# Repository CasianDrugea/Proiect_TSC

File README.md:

# Documentație Tehnică - InkTime Smartwatch
## Student: Drugea Casian 332CA

## 1. Descrierea Generală a Sistemului
Proiectul **InkTime** este un dispozitiv purtabil bazat pe microcontrolerul **nRF52840**, proiectat pentru a oferi o autonomie ridicată prin utilizarea unui ecran de tip E-Paper. Sistemul integrează funcționalități de monitorizare a mișcării, interfață haptică și un management avansat al energiei, fiind optimizat pentru dimensiuni reduse și eficiență.

## 2. Diagrama Bloc
Arhitectura hardware este structurată în jurul nucleului ARM Cortex-M4F, interconectat cu următoarele module:

* **Sistem de Procesare:** nRF52840 (Bluetooth 5.0, GPIO, SPI, I2C).
* **Afișaj:** E-Paper Display (EPD) cu circuit de drive integrat.
* **Senzori & Haptics:** Accelerometru BMA423 și Driver Haptic DRV2605.
* **Management Energie:** Încărcător LiPo BQ25180, Fuel Gauge MAX17048 și convertor DC/DC RT610A.
* **Interfață Utilizator:** Trei butoane de control (Up, Enter, Down).

## 3. Funcționalitate Hardware și Interfețe
Dispozitivul utilizează următoarele soluții tehnice pentru realizarea funcțiilor sale:

* **Microcontroler (nRF52840):** Gestionează stiva de comunicație Bluetooth și coordonează toți perifericii. S-a optat pentru acest model datorită consumului redus în modurile de repaus și a unității de calcul în virgulă mobila (FPU).
* **Afișaj E-Paper:** Este controlat prin interfața **SPI**. Circuitul de drive (bazat pe inductorul L5 și diodele MBR0530) asigură tensiunile necesare pentru actualizarea pixelilor.
* **Managementul Bateriei:**
    * **BQ25180:** Gestionează încărcarea prin USB-C și monitorizează curentul de intrare.
    * **MAX17048:** Monitorizează tensiunea celulei LiPo și oferă un algoritm de calcul al stării de încărcare (SoC) prin I2C.
    * **RT610A:** Un convertor Buck-Boost care stabilizează tensiunea la 3.3V, indiferent de nivelul de descărcare al bateriei.
* **Senzori și Actuatori:**
    * **BMA423:** Senzor de mișcare conectat prin I2C, utilizat pentru pedometru și gesturi.
    * **DRV2605:** Driver pentru motorul de vibrații, capabil să redea efecte haptice complexe.
* **Protecție și RF:** Linia USB-C este protejată de descărcări electrostatice prin **USBLC6-2SC6Y**. Antena ceramică de 2.4GHz este acordată prin componentele de matching (L4, C9) pentru o performanță optimă la 50 Ω.

## 4. Alocare Pini (Pinout nRF52840)

* **E-Paper (SPI):** `P0.14`, `P0.15`, `P0.17`, `P0.19`, `P0.20`, `P0.22` – Gestionează transferul datelor de imagine și semnalele de control (CS, BUSY, RES, DC).
* **I2C Bus (Shared):** `P0.26 (SDA)`, `P0.27 (SCL)` – Magistrală comună pentru senzorul IMU (BMA423), Fuel Gauge, Haptic Driver și Charger.
* **Butoane Fizice:** `P0.11`, `P0.12`, `P0.24` – Intrări digitale pentru butoanele de navigare UP, ENTER și DOWN.
* **Battery Charger:** `P0.02` – Pin de întrerupere (INT) pentru monitorizarea statusului de încărcare de la BQ25180.
* **Fuel Gauge:** `P0.03` – Linie de alertă pentru nivelul critic al bateriei de la MAX17048.
* **Crystal 32kHz:** `P0.00`, `P0.01` – Conexiuni dedicate XL1/XL2 pentru menținerea timpului în modurile Low Power.
* **Haptic Enable:** `P0.21` – Control GPIO pentru activarea driverului de vibrații DRV2605.
* **DC/DC Enable:** `P0.13` – Controlul regulatorului de tensiune pentru managementul energiei sistemului.
* **Debug Interface:** `SWDIO`, `SWDCLK` – Pini dedicați pentru programarea firmware-ului și depanare.
* **USB Native:** `D+`, `D-`, `VBUS` – Interfață pentru comunicație de date și detecția alimentării prin USB-C.

## 5. Fabricație și Fișiere de Producție
Dosarul proiectului include toate documentele necesare fabricării PCB-ului și asamblării (PCBA):

* **BOM (.bom):** Lista completă de componente cu link-uri către furnizori și coduri de comandă LCSC.
* **Gerber Files (.zip):** Straturile de cupru, masca de lipire, silkscreen-ul și fișierele de găurire (Drill).
* **Pick & Place (.cpl):** Coordonatele X-Y și rotația fiecărei componente pentru asamblarea automată.

## 6. Jurnal de Design și Decizii Tehnice
* **Utilizarea componentelor 0201:** Condensatorii de decuplare de sub nRF52840 sunt de mărime 0201 pentru a permite o rutare cât mai scurtă către masă și a economisi spațiu pe un PCB dens.
* **Traseele de alimentare și utilizarea VIA-urilor:** S-a optat pentru utilizarea trecerilor metalizate (vias) pe traseele de alimentare (V_BAT, 3.3V) pentru a facilita rutarea între straturi în zonele aglomerate. Justificarea tehnică rezidă în necesitatea de a menține o impedanță scăzută; în punctele de distribuție principală, s-au folosit mai multe via-uri în paralel pentru a crește capacitatea de transport a curentului și pentru a reduce inductanța parazită, prevenind astfel căderile de tensiune în timpul vârfurilor de consum (ex: refresh E-Ink sau transmisie RF).
* **Selecția Antenei:** S-a ales o antenă tip "Chip" pentru a reduce dimensiunea totală a carcasei, eliminând necesitatea unei antene imprimate pe PCB care ar fi ocupat o suprafață mai mare.
* **Erori de Suprapunere (Design Rule Check):** S-au ignorat erorile de suprapunere ale textului (silkscreen) în zonele critice ale conectorilor, prioritizând integritatea traseelor de semnal și a pad-urilor în detrimentul vizibilității etichetelor.

## 7. Structura Fișierelor
* `/Hardware`: Fișierele sursă `.sch` și `.brd`.
* `/Manufacturing`: Fișierele de producție (Gerber, BOM, CPL).
* `/Mechanical`: Modelul 3D al ansamblului complet (.step și .f3z).
* `/Images`: Randări ale dispozitivului și diagrame de sistem.

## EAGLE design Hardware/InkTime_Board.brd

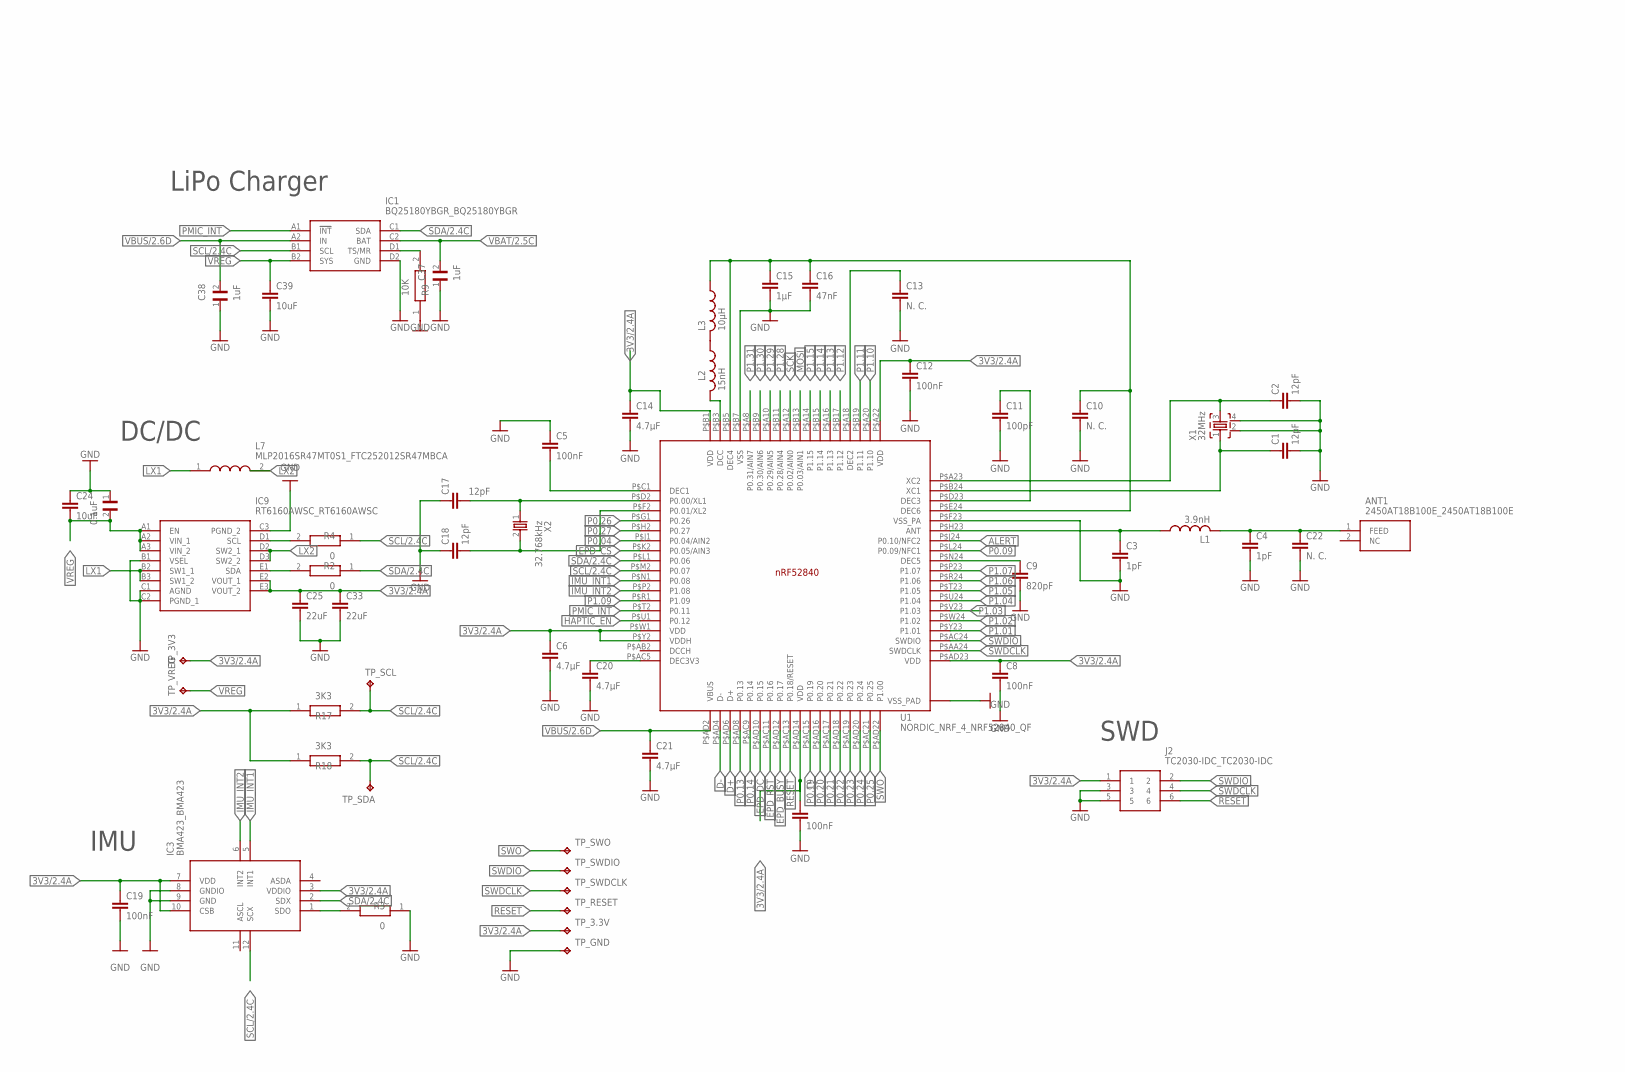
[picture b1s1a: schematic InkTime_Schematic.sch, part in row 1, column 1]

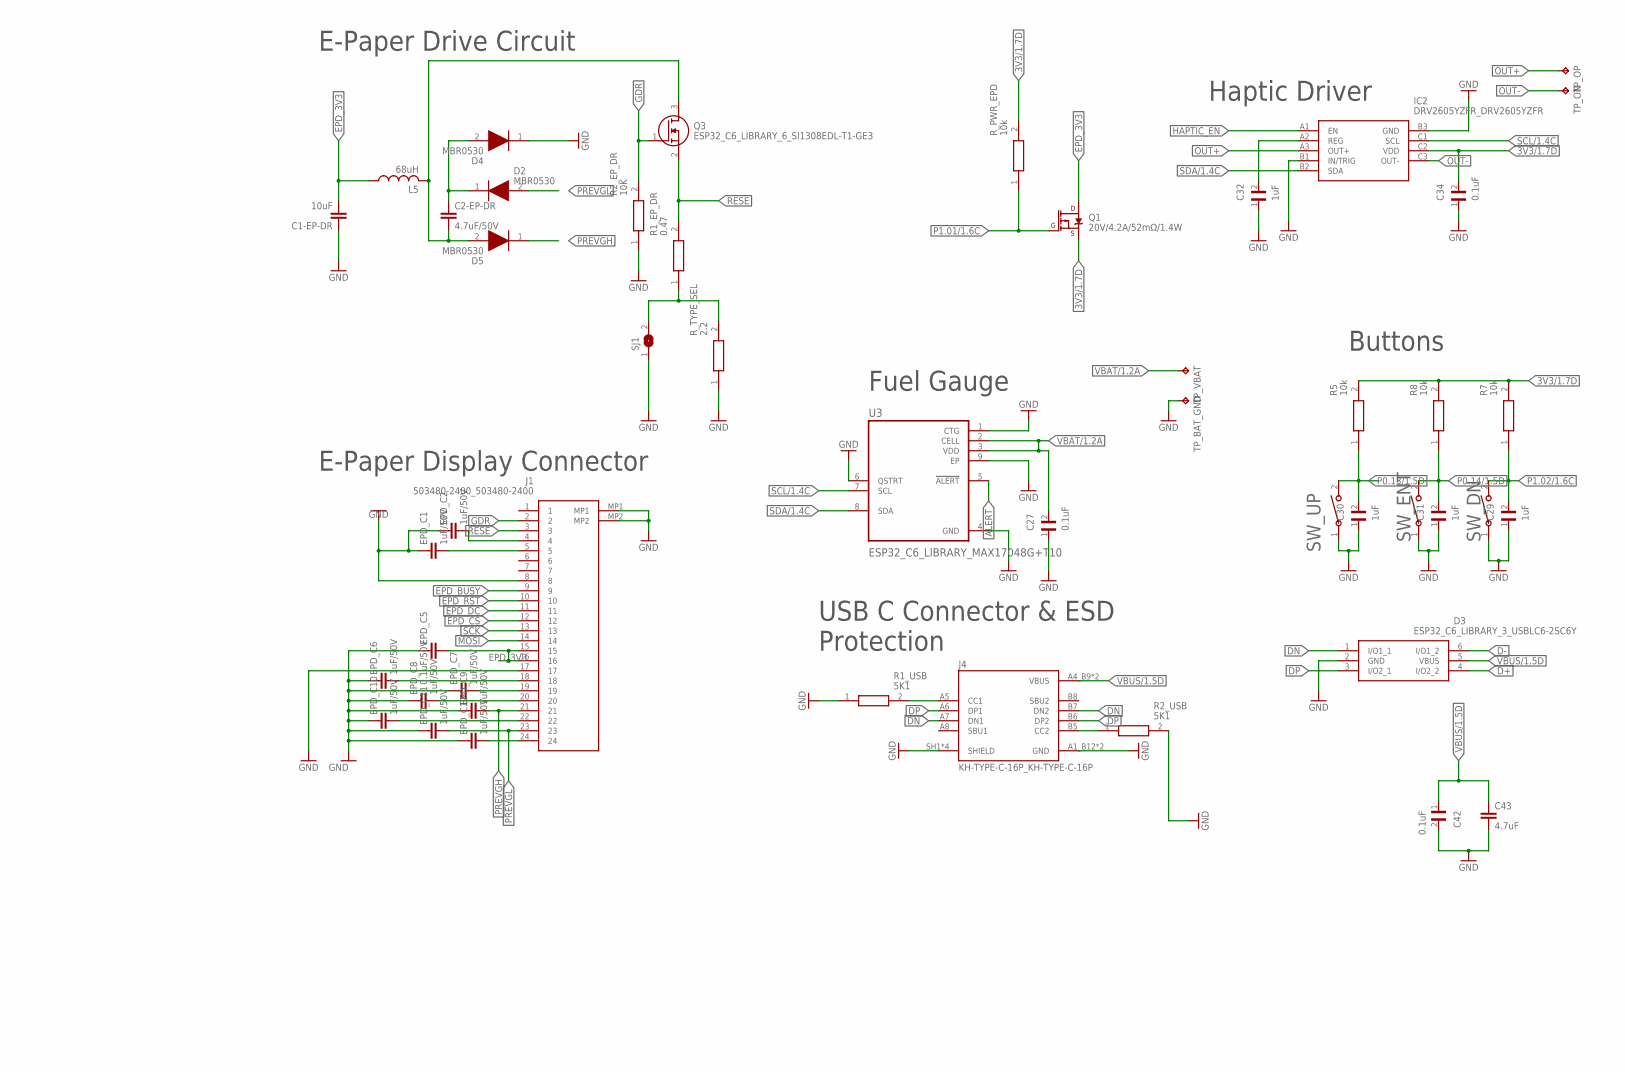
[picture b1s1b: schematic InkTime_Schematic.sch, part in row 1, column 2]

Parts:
ANT1: 2450AT18B100E_2450AT18B100E; 2450AT18B100E_ANTC3216X140N
C1, C2, C17, C18: 12pF; NORDIC_NRF_3_RESC0201_L
C1-EP-DR, C24, C39: 10uF; NORDIC_NRF_3_RESC0402_L
C2-EP-DR: 4.7uF/50V; NORDIC_NRF_3_RESC0402_L
C3, C4: 1pF; NORDIC_NRF_3_RESC0201_L
C5, C7, C8, C12, C19: 100nF; NORDIC_NRF_3_RESC0201_L
C6, C14, C20, C21: 4.7µF; NORDIC_NRF_3_RESC0402_L
C9: 820pF; NORDIC_NRF_3_RESC0201_L
C10, C13, C22: N. C.; NORDIC_NRF_3_RESC0201_L
C11: 100pF; NORDIC_NRF_3_RESC0201_L
C15: 1µF; NORDIC_NRF_3_RESC0402_L
C16: 47nF; NORDIC_NRF_3_RESC0201_L
C23, C27, C34, C42: 0.1uF; GRM011R60J152KE01L_1_0201
C25, C33: 22uF; NORDIC_NRF_3_RESC0402_L
C29, C30, C31, C32, C37, C38: 1uF; GRM011R60J152KE01L_1_0201
C43: 4.7uF; NORDIC_NRF_3_RESC0402_L
D2, D4, D5: MBR0530; ESP32_C6_LIBRARY_5_SOD3716X135N
D3: ESP32_C6_LIBRARY_3_USBLC6-2SC6Y; ESP32_C6_LIBRARY_3_SOT95P280X145-6N
EPD_C1, EPD_C2, EPD_C6, EPD_C7, EPD_C8, EPD_C9, EPD_C10, EPD_C11, EPD_C12: 1uF/50V; NORDIC_NRF_3_RESC0402_L
EPD_C5: 0.1uF/50V; NORDIC_NRF_3_RESC0201_L
IC1: BQ25180YBGR_BQ25180YBGR; BQ25180YBGR_BGA8C40P2X4_100X155X50
IC2: DRV2605YZFR_DRV2605YZFR; DRV2605YZFR_BGA9C50P3X3_144X144X62
IC3: BMA423_BMA423
IC9: RT6160AWSC_RT6160AWSC; RT6160AWSC_BGA15C40P3X5_140X230X60
J1: 503480-2400_503480-2400; 503480-2400_5034802400
J2: TC2030-IDC_TC2030-IDC; TC2030-IDC_TC2030IDC
J4: KH-TYPE-C-16P_KH-TYPE-C-16P; KH-TYPE-C-16P_KINGHELM_KH-TYPE-C-16P
L1: 3.9nH; NORDIC_NRF_2_RESC0201_L
L2: 15nH; NORDIC_NRF_2_RESC0201_L
L3: 10µH; NORDIC_NRF_2_RESC0603_L
L5: 68uH; NORDIC_NRF_2_RESC0805_L
L7: MLP2016SR47MT0S1_FTC252012SR47MBCA; MLP2016SR47MT0S1_INDC2016X100N
Q1: 20V/4.2A/52mΩ/1.4W; ESP32_C6_LIBRARY_4_ESP32_C6_LIBRARY_4_ESP32_C6_LIBRARY_4_ES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
Q3: ESP32_C6_LIBRARY_6_SI1308EDL-T1-GE3; ESP32_C6_LIBRARY_6_SOT65P210X110-3N
R1_EP_DR: 0.47; ERA-1AEB3401C_0201
R1_USB, R2_USB: 5K1; ERA-1AEB3401C_0201
R2, R3, R4: 0; CPF0201D7K68C1_0201
R2_EP_DR: 10K; ERA-1AEB3401C_0201
R5, R7, R8: 10k; ERA-1AEB3401C_0201
R9: 10K; CPF0201D7K68C1_0201
R17, R18: 3K3; CPF0201D7K68C1_0201
R_PWR_EPD: 10k; ERA-1AEB3401C_0201
R_TYPE_SEL: 2.2; ERA-1AEB3401C_0201
SJ1: ESP32_C6_LIBRARY_7_JUMPER_SJ
SW_DN: 2025-10-22_07-23-44_LIBRARY_EVP-AKE31ASW_EVP-AKE3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; 2025-10-22_07-23-44_LIBRARY_SW_EVP-AKE31A_PAN
SW_ENT: 2025-10-22_07-23-44_LIBRARY_EVP-AKE31ASW_EVP-AKE3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; 2025-10-22_07-23-44_LIBRARY_SW_EVP-AKE31A_PAN
SW_UP: 2025-10-22_07-23-44_LIBRARY_EVP-AKE31ASW_EVP-AKE3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; 2025-10-22_07-23-44_LIBRARY_SW_EVP-AKE31A_PAN
TP_3.3V, TP_3V3: HECTOR_WATCH_1_TPTP20R; HECTOR_WATCH_1_TP20R
TP_BAT_GND: HECTOR_WATCH_1_TPTP20R; HECTOR_WATCH_1_TP20R
TP_GND: HECTOR_WATCH_1_TPTP20R; HECTOR_WATCH_1_TP20R
TP_ON: HECTOR_WATCH_1_TPTP20R; HECTOR_WATCH_1_TP20R
TP_OP: HECTOR_WATCH_1_TPTP20R; HECTOR_WATCH_1_TP20R
TP_RESET: HECTOR_WATCH_1_TPTP20R; HECTOR_WATCH_1_TP20R
TP_SCL: HECTOR_WATCH_1_TPTP20R; HECTOR_WATCH_1_TP20R
TP_SDA: HECTOR_WATCH_1_TPTP20R; HECTOR_WATCH_1_TP20R
TP_SWDCLK: HECTOR_WATCH_1_TPTP20R; HECTOR_WATCH_1_TP20R
TP_SWDIO: HECTOR_WATCH_1_TPTP20R; HECTOR_WATCH_1_TP20R
TP_SWO: HECTOR_WATCH_1_TPTP20R; HECTOR_WATCH_1_TP20R
TP_VBAT: HECTOR_WATCH_1_TPTP20R; HECTOR_WATCH_1_TP20R
TP_VREG: HECTOR_WATCH_1_TPTP20R; HECTOR_WATCH_1_TP20R
U1: NORDIC_NRF_4_NRF52840_QF; NORDIC_NRF_4_AQFN50P700X700X85_HS-74N
U3: ESP32_C6_LIBRARY_MAX17048G+T10; ESP32_C6_LIBRARY_SON50P200X200X80-9N
X1: 32MHz; NORDIC_NRF_BT-XTAL_2016_N
X2: 32.768kHz; NORDIC_NRF_1_XTAL_3215_N

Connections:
3V3/1.7D: C34.2, IC2.C2 (VDD), Q1.2 (S), R5.2, R7.2, R8.2, R_PWR_EPD.2
3V3/2.4A: C6.1, C7.1, C8.1, C12.1, C14.1, C19.1, C25.1, C33.1, IC3.3 (VDDIO), IC3.7 (VDD), IC3.10 (CSB), IC9.E2 (VOUT_1), IC9.E3 (VOUT_2), J2.1, R17.1, R18.1, TP_3.3V.TP, TP_3V3.TP, U1.P$A22 (VDD), U1.P$AD14 (VDD), U1.P$AD23 (VDD), U1.P$B1 (VDD), U1.P$W1 (VDD), U1.P$Y2 (VDDH)
ALERT: U1.P$J24 (P0.10/NFC2), U3.5 (!ALERT)
D+: D3.4 (I/O2_2), U1.P$AD6 (D+)
D-: D3.6 (I/O1_2), U1.P$AD4 (D-)
DN: D3.1 (I/O1_1), J4.A7 (DN1), J4.B7 (DN2)
DP: D3.3 (I/O2_1), J4.A6 (DP1), J4.B6 (DP2)
EPD_3V3: C1-EP-DR.2, EPD_C5.2, J1.15, J1.16, L5.1, Q1.3 (D)
EPD_BUSY: J1.9, U1.P$AD12 (P0.17)
EPD_CS: J1.12, U1.P$K2 (P0.05/AIN3)
EPD_DC: J1.11, U1.P$AD10 (P0.15)
EPD_RST: J1.10, U1.P$AC11 (P0.16)
GDR: J1.2, Q3.1 (G), R2_EP_DR.2
GND: C1.2, C1-EP-DR.1, C2.2, C3.2, C4.2, C5.1, C6.2, C7.2, C8.2, C9.2, C10.2, C11.2, C12.2, C13.2, C14.2, C15.2, C16.2, C17.1, C18.1, C19.2, C20.2, C21.2, C22.2, C23.1, C24.1, C25.2, C27.1, C29.1, C30.1, C31.1, C32.1, C33.2, C34.1, C37.1, C38.1, C39.2, C42.2, C43.2, D3.2 (GND), D4.1 (K), EPD_C1.1, EPD_C2.1, EPD_C5.1, EPD_C6.1, EPD_C7.1, EPD_C8.1, EPD_C9.1, EPD_C10.1, EPD_C11.1, EPD_C12.1, IC1.D2 (GND), IC2.B1 (IN/TRIG), IC2.B3 (GND), IC3.8 (GNDIO), IC3.9 (GND), IC9.B1 (VSEL), IC9.C1 (AGND), IC9.C2 (PGND_1), IC9.C3 (PGND_2), J1.8, J1.17, J1.MP1, J1.MP2, J2.3, J2.5, J4.A1_B12 (GND), J4.A12_B1 (GND), J4.SH1 (SHIELD), J4.SH2 (SHIELD), J4.SH3 (SHIELD), J4.SH4 (SHIELD), R1_USB.1, R2_EP_DR.1, R2_USB.2, R3.1, R9.1, R_TYPE_SEL.1, SJ1.1, SW_DN.1, SW_ENT.1, SW_UP.1, TP_BAT_GND.TP, TP_GND.TP, U1.P$74 (VSS_PAD), U1.P$75 (VSS_PAD), U1.P$76 (VSS_PAD), U1.P$77 (VSS_PAD), U1.P$78 (VSS_PAD), U1.P$79 (VSS_PAD), U1.P$80 (VSS_PAD), U1.P$81 (VSS_PAD), U1.P$82 (VSS_PAD), U1.P$83 (VSS_PAD), U1.P$84 (VSS_PAD), U1.P$85 (VSS_PAD), U1.P$86 (VSS_PAD), U1.P$87 (VSS_PAD), U1.P$88 (VSS_PAD), U1.P$89 (VSS_PAD), U1.P$90 (VSS_PAD), U1.P$B7 (VSS), U1.P$F23 (VSS_PA), U3.1 (CTG), U3.4 (GND), U3.6 (QSTRT), U3.9 (EP), X1.2, X1.4
HAPTIC_EN: IC2.A1 (EN), U1.P$U1 (P0.12)
IMU_INT1: IC3.5 (INT1), U1.P$N1 (P0.08)
IMU_INT2: IC3.6 (INT2), U1.P$P2 (P1.08)
LX1: IC9.B2 (SW1_1), IC9.B3 (SW1_2), L7.1
LX2: IC9.D2 (SW2_1), IC9.D3 (SW2_2), L7.2
MOSI: J1.14, U1.P$B13 (P0.03/AIN1)
unnamed: C5.2, U1.P$C1 (DEC1)
unnamed: L2.2, U1.P$B3 (DCC)
unnamed: L2.1, L3.2
unnamed: C2.1, U1.P$A23 (XC2), X1.3
unnamed: C20.1, U1.P$AC5 (DEC3V3)
unnamed: C9.1, U1.P$N24 (DEC5)
unnamed: C11.1, U1.P$D23 (DEC3)
unnamed: C13.1, U1.P$A18 (DEC2)
unnamed: C3.1, L1.1, U1.P$H23 (ANT)
unnamed: C10.1, C15.1, C16.1, L3.1, U1.P$B5 (DEC4), U1.P$E24 (DEC6)
unnamed: ANT1.1 (FEED), C4.1, C22.1, L1.2
unnamed: C1.1, U1.P$B24 (XC1), X1.1
unnamed: C17.2, U1.P$D2 (P0.00/XL1), X2.1
unnamed: C18.2, U1.P$F2 (P0.01/XL2), X2.2
unnamed: IC1.D1 (TS/MR), R9.2
unnamed: IC9.E1 (SDA), R2.2
unnamed: IC9.D1 (SCL), R4.2
unnamed: IC3.1 (SDO), R3.2
unnamed: C32.2, IC2.A2 (REG)
unnamed: J4.A5 (CC1), R1_USB.2
unnamed: J4.B5 (CC2), R2_USB.1
unnamed: EPD_C2.2, J1.4
unnamed: EPD_C1.2, J1.5
unnamed: EPD_C6.2, J1.18
unnamed: EPD_C7.2, J1.19
unnamed: EPD_C8.2, J1.20
unnamed: EPD_C10.2, J1.22
unnamed: EPD_C12.2, J1.24
unnamed: C2-EP-DR.2, D5.2 (A), L5.2, Q3.3 (D)
unnamed: C2-EP-DR.1, D2.1 (K), D4.2 (A)
unnamed: R1_EP_DR.1, R_TYPE_SEL.2, SJ1.2
OUT+: IC2.A3 (OUT+), TP_OP.TP
OUT-: IC2.C3 (OUT-), TP_ON.TP
P0.04: U1.P$J1 (P0.04/AIN2)
P0.09: U1.P$L24 (P0.09/NFC1)
P0.13: U1.P$AD8 (P0.13)
P0.13/1.5D: C30.2, R5.1, SW_UP.2
P0.14: U1.P$AC9 (P0.14)
P0.14/1.5D: C31.2, R8.1, SW_ENT.2
P0.19: U1.P$AC15 (P0.19)
P0.20: U1.P$AD16 (P0.20)
P0.21: U1.P$AC17 (P0.21)
P0.22: U1.P$AD18 (P0.22)
P0.23: U1.P$AC19 (P0.23)
P0.24: U1.P$AD20 (P0.24)
P0.25: U1.P$AC21 (P0.25)
P0.26: U1.P$G1 (P0.26)
P0.27: U1.P$H2 (P0.27)
P1.01: U1.P$Y23 (P1.01)
P1.01/1.6C: Q1.1 (G), R_PWR_EPD.1
P1.02: U1.P$W24 (P1.02)
P1.02/1.6C: C29.2, R7.1, SW_DN.2
P1.03: U1.P$V23 (P1.03)
P1.04: U1.P$U24 (P1.04)
P1.05: U1.P$T23 (P1.05)
P1.06: U1.P$R24 (P1.06)
P1.07: U1.P$P23 (P1.07)
P1.09: U1.P$R1 (P1.09)
P1.10: U1.P$A20 (P1.10)
P1.11: U1.P$B19 (P1.11)
P1.12: U1.P$B17 (P1.12)
P1.13: U1.P$A16 (P1.13)
P1.14: U1.P$B15 (P1.14)
P1.15: U1.P$A14 (P1.15)
P1.28: U1.P$B11 (P0.28/AIN4)
P1.29: U1.P$A10 (P0.29/AIN5)
P1.30: U1.P$B9 (P0.30/AIN6)
P1.31: U1.P$A8 (P0.31/AIN7)
PMIC_INT: IC1.A1 (!INT), U1.P$T2 (P0.11)
PREVGH: D5.1 (K), EPD_C9.2, J1.21
PREVGL: D2.2 (A), EPD_C11.2, J1.23
RESE: J1.3, Q3.2 (S), R1_EP_DR.2
RESET: J2.6, TP_RESET.TP, U1.P$AC13 (P0.18/RESET)
SCK: J1.13, U1.P$A12 (P0.02/AIN0)
SCL/1.4C: IC2.C1 (SCL), U3.7 (SCL)
SCL/2.4C: IC1.B1 (SCL), IC3.12 (SCX), R4.1, R17.2, R18.2, TP_SCL.TP, TP_SDA.TP, U1.P$M2 (P0.07)
SDA/1.4C: IC2.B2 (SDA), U3.8 (SDA)
SDA/2.4C: IC1.C1 (SDA), IC3.2 (SDX), R2.1, U1.P$L1 (P0.06)
SWDCLK: J2.4, TP_SWDCLK.TP, U1.P$AA24 (SWDCLK)
SWDIO: J2.2, TP_SWDIO.TP, U1.P$AC24 (SWDIO)
SWO: TP_SWO.TP, U1.P$AD22 (P1.00)
VBAT/1.2A: C27.2, TP_VBAT.TP, U3.2 (CELL), U3.3 (VDD)
VBAT/2.5C: C37.2, IC1.C2 (BAT)
VBUS/1.5D: C42.1, C43.1, D3.5 (VBUS), J4.A4_B9 (VBUS), J4.A9_B4 (VBUS)
VBUS/2.6D: C21.1, C38.2, IC1.A2 (IN), U1.P$AD2 (VBUS)
VREG: C23.2, C24.2, C39.1, IC1.B2 (SYS), IC9.A1 (EN), IC9.A2 (VIN_1), IC9.A3 (VIN_2), TP_VREG.TP

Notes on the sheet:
LiPo Charger
DC/DC
IMU
SWD
E-Paper Display Connector
E-Paper Drive Circuit
Haptic Driver
Fuel Gauge
USB C Connector & ESD Protection
Buttons

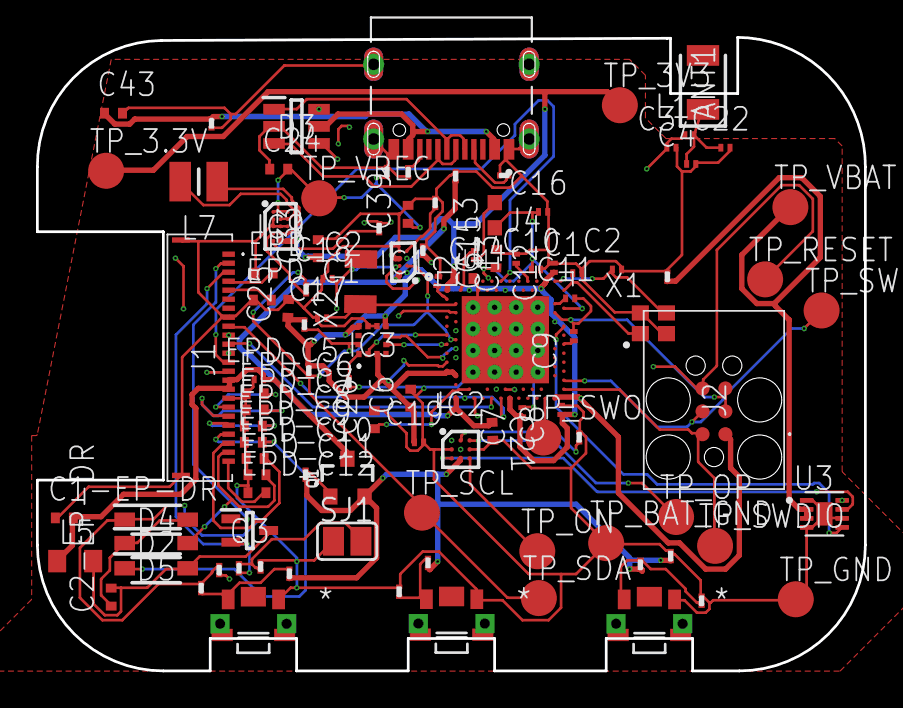
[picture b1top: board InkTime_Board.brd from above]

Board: 4 copper layers, 46.0 x 35.2 mm, 105 parts (0 on the bottom side), 75 nets.

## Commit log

2026-04-09 For review
2026-04-20 after review

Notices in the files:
parts and their libraries:
COPYRIGHT: Copyright (C) 2025 Ultra Librarian. All rights reserved.
